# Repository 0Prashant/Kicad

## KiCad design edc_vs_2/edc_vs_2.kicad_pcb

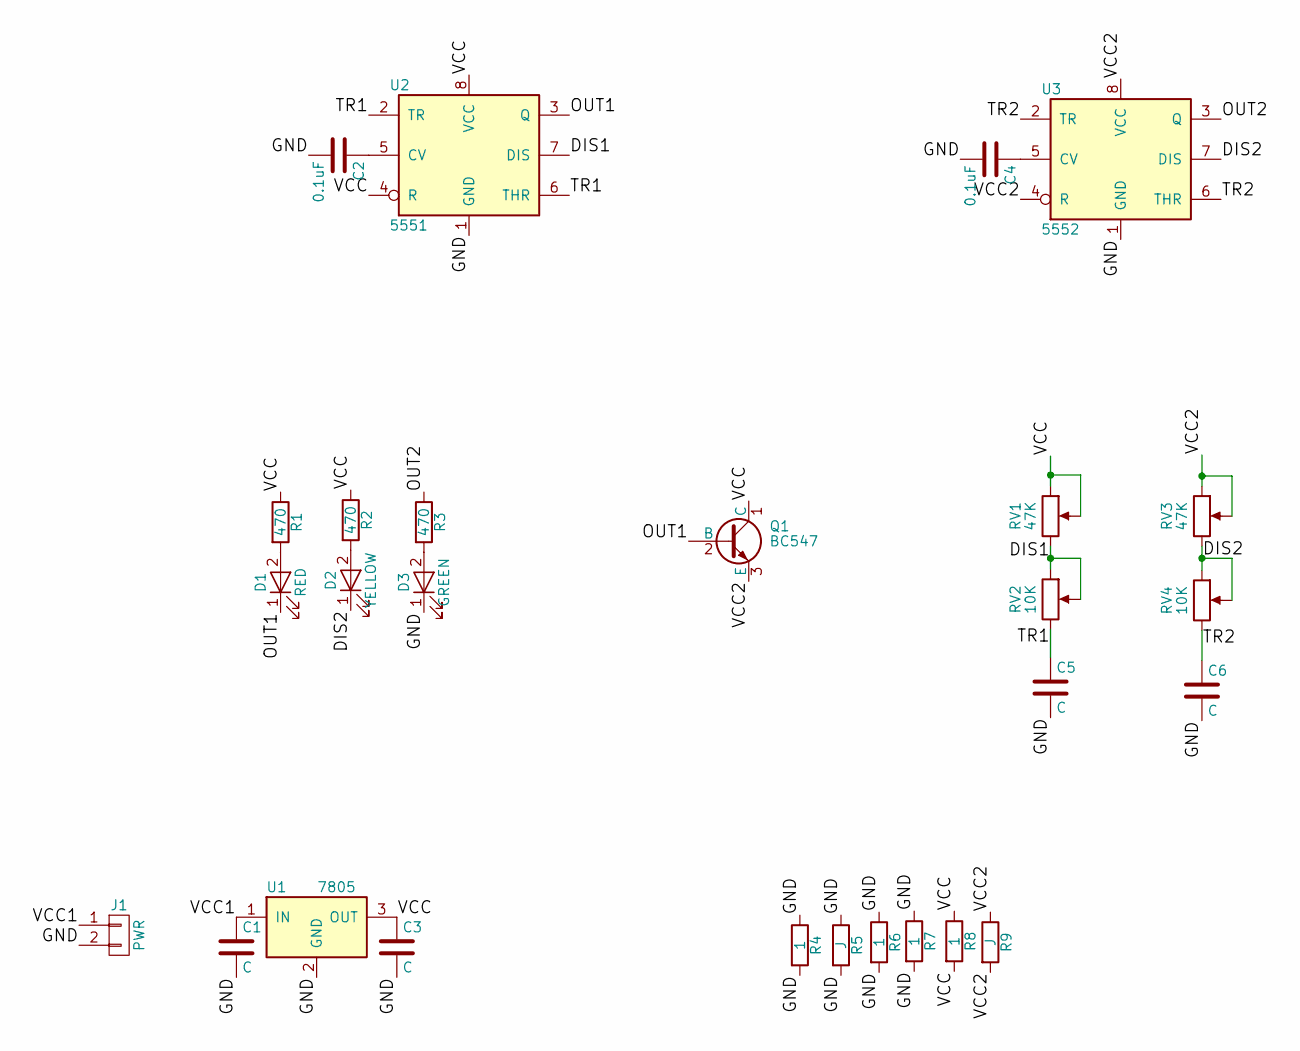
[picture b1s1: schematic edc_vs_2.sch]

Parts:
C1, C3, C5, C6: C; Capacitor_100uF
C2: 0.1uF; C_Disc_D3.0mm_W2.0mm_P2.50mm
C4: 0.1uF; C_Disc_D3.0mm_W1.6mm_P2.50mm
D1: RED; LED_D5.0mm
D2: YELLOW; LED_D5.0mm
D3: GREEN; LED_D5.0mm
J1: PWR; Bornier2
Q1: BC547; TO-92_Molded_Narrow
R1, R2, R3: 470; R_Axial_DIN0207_L6.3mm_D2.5mm_P7.62mm_Horizontal
R4, R6, R7, R8: 1; R_Axial_DIN0207_L6.3mm_D2.5mm_P7.62mm_Horizontal
R5, R9: J; R_Axial_DIN0207_L6.3mm_D2.5mm_P7.62mm_Horizontal
RV1, RV3: 47K; Potentiometer_Triwood_RM-065
RV2, RV4: 10K; Potentiometer_Triwood_RM-065
U1: 7805; TO-220_Vertical
U2: 5551; DIP-8_W7.62mm
U3: 5552; DIP-8_W7.62mm

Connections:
/DIS1: RV1.3, RV2.1, RV2.2, U2.7 (DIS)
/DIS2: D2.1 (K), RV3.3, RV4.1, RV4.2, U3.7 (DIS)
/GND: C1.2, C2.2, C3.2, C4.2, C5.2, C6.2, D3.1 (K), J1.2, R4.1, R4.2, R5.1, R5.2, R6.1, R6.2, R7.1, R7.2, U1.2 (GND), U2.1 (GND), U3.1 (GND)
/OUT1: D1.1 (K), Q1.2 (B), U2.3 (Q)
/OUT2: R3.1, U3.3 (Q)
/TR1: C5.1, RV2.3, U2.2 (TR), U2.6 (THR)
/TR2: C6.1, RV4.3, U3.2 (TR), U3.6 (THR)
/VCC: C3.1, Q1.1 (C), R1.1, R2.1, R8.1, R8.2, RV1.1, RV1.2, U1.3 (OUT), U2.4 (R), U2.8 (VCC)
/VCC1: C1.1, J1.1, U1.1 (IN)
/VCC2: Q1.3 (E), R9.1, R9.2, RV3.1, RV3.2, U3.4 (R), U3.8 (VCC)
unnamed: C2.1, U2.5 (CV)
unnamed: C4.1, U3.5 (CV)
unnamed: D1.2 (A), R1.2
unnamed: D2.2 (A), R2.2
unnamed: D3.2 (A), R3.2

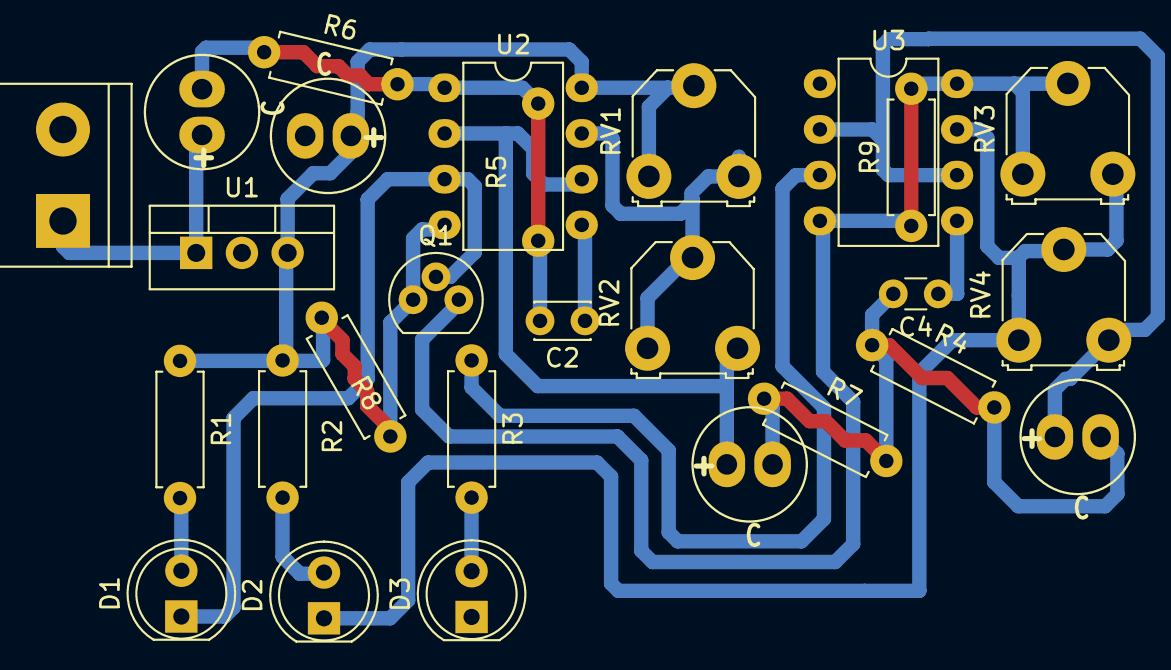
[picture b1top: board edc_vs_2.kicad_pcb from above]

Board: 2 copper layers, 27 parts (0 on the bottom side), 15 nets.

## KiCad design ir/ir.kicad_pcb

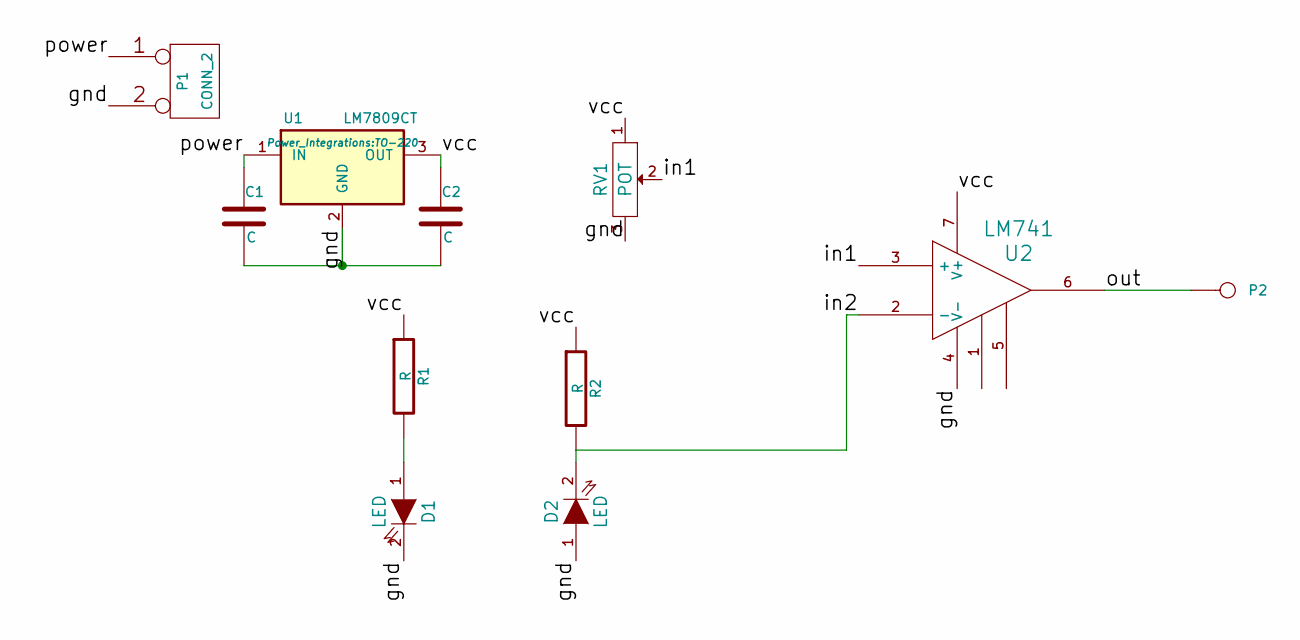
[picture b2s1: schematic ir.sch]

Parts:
C1: C; CP_Radial_D6.3mm_P2.50mm
C2: C; CP_Radial_D5.0mm_P2.50mm
D1, D2: LED; LED_D3.0mm
P1: CONN_2; Pin_Header_Straight_1x02_Pitch2.54mm
P2: CONN_1; Pin_Header_Straight_1x01_Pitch2.54mm
R1, R2: R; R_Axial_DIN0207_L6.3mm_D2.5mm_P7.62mm_Horizontal
RV1: POT; Potentiometer_Trimmer_ACP_CA9VSMD_Horizontal_Px9.2mm_Py5.0m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
U1: LM7809CT; TO-220
U2: LM741; DIP-8_W7.62mm_Socket

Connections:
/gnd: C1.2, C2.2, D1.2 (K), D2.1 (A), P1.2 (PM), RV1.3, U1.2 (GND), U2.4 (V-)
/in1: RV1.2, U2.3 (+)
/in2: D2.2 (K), R2.2, U2.2 (-)
/out: P2.1, U2.6
/power: C1.1, P1.1, U1.1 (IN)
/vcc: C2.1, R1.1, R2.1, RV1.1, U1.3 (OUT), U2.7 (V+)
unnamed: D1.1 (A), R1.2

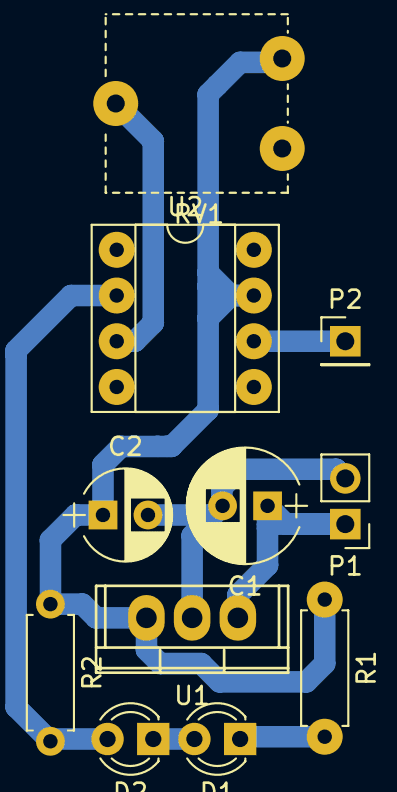
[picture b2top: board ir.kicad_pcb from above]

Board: 2 copper layers, 11 parts (0 on the bottom side), 7 nets.

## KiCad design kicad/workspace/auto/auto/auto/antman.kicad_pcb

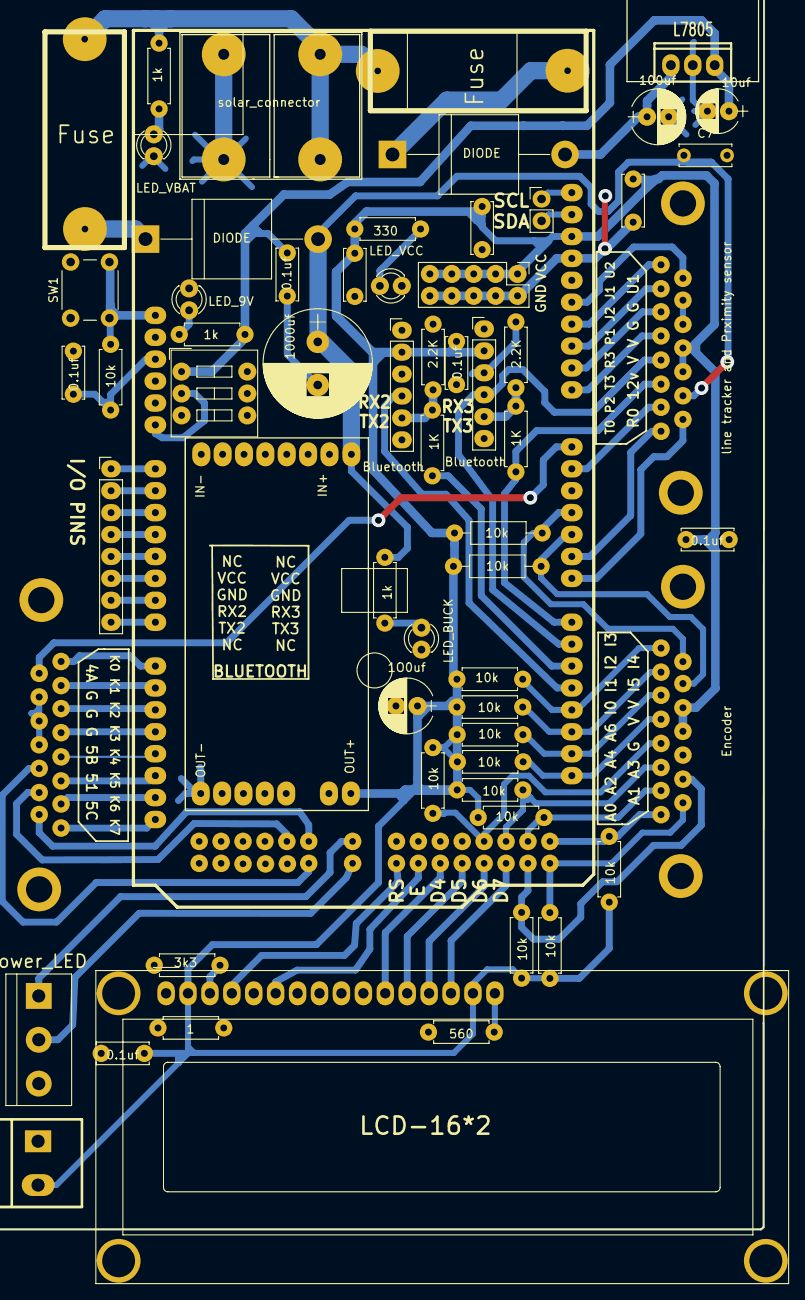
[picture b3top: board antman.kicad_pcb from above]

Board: 2 copper layers, 62 parts (0 on the bottom side), 71 nets.

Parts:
C1, C2, C3, C4, C5, C6, C8: 0.1uf; C_Disc_D6.0mm_W2.5mm_P5.00mm
C7, C9: C; C_Disc_D6.0mm_W2.5mm_P5.00mm
C10: 100uf; Cap_100uF
C11: 1000uf; Cao_1000uF
C12: 10uf; Cap_10uF
C13: 1O0uf; Cap_100uF
D1: LED_VBAT; LED_D3.0mm
D2: LED_9V; LED_D3.0mm
D3, D4: DIODE; D_P600_R-6_P20.00mm_Horizontal
D5: LED_VCC; LED_D3.0mm
D6: LED_BUCK; LED_D3.0mm
DS1: LCD-16*2
F1, F2: Fuse; FUSE
J1: VCC_GND; Pin_Header_Straight_2x05_Pitch2.54mm
J2, J5: Bluetooth; Pin_Header_Straight_1x06_Pitch2.54mm
J3: Motor; DB15FC
J4: Power_LED; bornier3
J6: Encoder; DB15FC
J7: I/O Pins; Pin_Header_Straight_1x08_Pitch2.54mm
J8: Conn_01x02; Pin_Header_Straight_1x02_Pitch2.54mm
J9: line tracker and Prximity sensor; DB15FC
J10: solar_connector; SolarConn
J11: Conn_01x02; bornier2-medium
R1, R3: 1K; Res_Small
R2, R4: 2.2K; Res_Small
R5: 560; Res_Small
R6, R7, R8, R9, R10, R19, R20, R21, R22, R23, R24: 10k; Res_Small
R11, R12: 10k; R_Axial_DIN0207_L6.3mm_D2.5mm_P10.16mm_Horizontal
R13, R14, R16: 1k; Res_Small
R15: 330; Res_Small
R18: 3k3; Res_Small
R25: 1; Res_Small
SW1: SW_Push; SW_PUSH_6mm
SW2: SW_DIP_x01; SW_DIP_x3_W7.62mm_Slide
U1: Arduino_Mega; ARDUINO_MEGA_SHIELD
U2: L7805; LM78_heatsink
U3: LM2596-PSU; Buck

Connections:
+9V: C8.2, C12.1, R14.2, SW2.1, U2.3
+12V: F1.2, F2.2, J10.2, R13.2
/5V: C1.2, R10.1, U1.5V
/12vv: C7.1, C11.1, D4.2, J9.14, R16.2, U3.1
/E: DS1.6, U1.35
/INT0: J6.4, J8.1, R6.2, U1.21
/INT1: J6.3, J8.2, R7.2, U1.20
/INT2: J6.2, R8.2, U1.19
/INT3: J6.1, R9.2, U1.18
/INT4: J6.10, R11.2, U1.2
/INT5: J6.9, R12.2, U1.3
/JPULSE1: J9.2, U1.10
/JPULSE2: J9.3, U1.9
/OC3A: J9.7, U1.5
/OC4A: J3.15, U1.6
/OC4C: J9.4, U1.8
/OC5A: J3.10, U1.46
/OC5B: J3.11, U1.45
/OC5C: J3.9, U1.44
/PA0: J6.8, R19.2, U1.22
/PA1: J6.15, R20.1, U1.23
/PA2: J6.7, R21.1, U1.24
/PA3: J6.14, R22.1, U1.25
/PA4: J6.6, R23.1, U1.26
/PA5: DS1.14, U1.27
/PA6: J6.5, R24.1, U1.28
/PA7: DS1.13, U1.29
/PC0: DS1.4, U1.37
/PC4: DS1.11, U1.33
/PC6: DS1.12, U1.31
/PF0: J7.1, U1.AD0
/PF1: J7.2, U1.AD1
/PF2: J7.3, U1.AD2
/PF3: J7.4, U1.AD3
/PF4: J7.5, U1.AD4
/PF5: J7.6, U1.AD5
/PF6: J7.7, U1.AD6
/PF7: J7.8, U1.AD7
/PG0: J4.2, U1.41
/PG1: J4.1, U1.40
/PK0: J3.8, U1.AD8
/PK1: J3.7, U1.AD9
/PK2: J3.6, U1.AD10
/PK3: J3.5, U1.AD11
/PK4: J3.4, U1.AD12
/PK5: J3.3, U1.AD13
/PK6: J3.2, U1.AD14
/PK7: J3.1, U1.AD15
/RESET: R10.2, SW1.2, U1.RST
/RX0: J9.15, U1.0
/RX2: J2.4, U1.17
/RX3: J5.4, J9.5, U1.15
/TX0: J9.8, U1.1
/TX2: R1.1, U1.16
/TX3: J9.6, R3.1, U1.14
/UEN1: J9.9, U1.12
/UEN2: J9.1, U1.11
/VIN: SW2.2, U1.V_IN
GND: C1.1, C2.1, C3.2, C4.1, C5.2, C6.2, C7.2, C8.1, C9.1, C10.2, C11.2, C12.2, C13.2, D1.1, D2.1, D5.1, D6.1, DS1.1, DS1.5, J1.2, J1.4, J1.6, J1.8, J1.10, J2.3, J3.12, J3.13, J3.14, J4.3, J5.3, J6.13, J9.10, J9.11, J10.1, J11.1, R2.2, R4.2, R5.1, R18.2, R25.1, R25.2, SW1.1, U1.GND3, U2.2, U3.2, U3.3
unnamed: C10.1, D3.2, U2.1
unnamed: D1.2, R13.1
unnamed: D2.2, R14.1
unnamed: D3.1, F1.1
unnamed: D4.1, F2.1
unnamed: D5.2, R15.2
unnamed: D6.2, R16.1
unnamed: DS1.3, R18.1
unnamed: DS1.16, R5.2
unnamed: J2.5, R1.2, R2.1
unnamed: J5.5, R3.2, R4.1
VCC: C2.2, C3.1, C4.2, C5.1, C6.1, C9.2, C13.1, DS1.2, DS1.15, J1.1, J1.3, J1.5, J1.7, J1.9, J2.2, J5.2, J6.11, J6.12, J9.12, J9.13, J11.2, R6.1, R7.1, R8.1, R9.1, R11.1, R12.1, R15.1, R19.1, R20.2, R21.2, R22.2, R23.2, R24.2, U1.AREF, U3.4
